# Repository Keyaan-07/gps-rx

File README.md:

# GPS Receiver
GPS-RX is a custom-hardware, low-power GPS receiver that is just 16x16mm in size. This receiver does not have any COCOM limits and is fully customisable. It uses UART to communicate with other external controllers and takes a 3.3 volt input. Unlike other GPS receivers, there are no speed or height based limits and can go to any height or any speeds. It is built like a really small module and can be built and assembled by anyone and used basically everywhere. I built this project to learn verilog and also because this seems really cool! The ice40up5k from lattice semiconductor is the FPGA that processes the GPS signals. 

### Assembly instructions
1. Order the PCB from the gerber files in the [production](/hardware/production/) folder. Get two stencils(one for the top and one for the bottom).
2. Either get PCBA, or solder the components yourself. 
3. If soldering yourself, place the top side stencil over the top side and apply paste. Place all the components. 
4. Reflow the top side. 
5. Do the same process for the bottom side!
6. Program the firmware by connecting to the test points. 
7. Your receiver is ready!

### Note about firmware: GPS firmware development without the actual board will be really hard, thus i am not writing the firmware right now. 

## BOM
|Designator                         |Function                    |Value              |Footprint                                  |Quantity|Price        |Amount|Link                                                                                                                                |
|-----------------------------------|----------------------------|-------------------|-------------------------------------------|--------|-------------|------|------------------------------------------------------------------------------------------------------------------------------------|
|PCB+stencil                        |PCB+stencil                 |Front and back both|16x16mm                                    |5+2     |2.1+6.14     |8.24  |https://jlcpcb.com/                                                                                                                 |
|C11, C9                            |Capacitor                   |100p               |402                                        |50      |0.0112       |0.56  |https://www.lcsc.com/product-detail/C77177.html                                                                                     |
|C12, C13, C14, C15, C18, C2, C4, C8|Capacitor                   |100n               |402                                        |100     |0.0067       |0.67  |https://www.lcsc.com/product-detail/C60474.html                                                                                     |
|C19                                |Capacitor                   |27p                |402                                        |100     |0.0036       |0.36  |https://www.lcsc.com/product-detail/C1557.html                                                                                      |
|C20, C23, C24, C3, C5              |Capacitor                   |470p               |402                                        |50      |0.0176       |0.88  |https://www.lcsc.com/product-detail/C76971.html                                                                                     |
|C21, C22                           |Capacitor                   |10u                |603                                        |10      |0.04         |0.4   |https://www.lcsc.com/product-detail/C18164635.html                                                                                  |
|C6                                 |Capacitor                   |10n                |402                                        |100     |0.0041       |0.41  |https://www.lcsc.com/product-detail/C5137480.html                                                                                   |
|D1                                 |LED                         |LED                |402                                        |20      |0.0357       |0.714 |https://www.lcsc.com/product-detail/C5123495.html                                                                                   |
|FL1                                |Filter                      |SAFFB1G56KB0F0A    |Filter_1109-5_1.1x0.9mm                    |10      |0.072        |0.72  |https://www.lcsc.com/product-detail/C91647.html                                                                                     |
|J1, J2                             |Connector                   |Conn_Coaxial_Small |U.FL_Molex_MCRF_73412-0110_Vertical        |5       |0.1019       |0.51  |https://www.lcsc.com/product-detail/C88374.html                                                                                     |
|J3                                 |Connector                   |Conn_01x04_Pin     |PinHeader_1x04_P2.54mm_Vertical            |20      |0.026        |0.52  |https://www.lcsc.com/product-detail/C2691448.html                                                                                   |
|L1                                 |Inductor                    |27n                |402                                        |10      |0.09         |0.9   |https://www.lcsc.com/product-detail/C882469.html                                                                                    |
|L2                                 |Inductor                    |2.2u               |402                                        |5       |0.304        |1.52  |https://www.lcsc.com/product-detail/C3911260.html                                                                                   |
|R1, R2, R6                         |Resistor                    |10k                |402                                        |100     |0.0025       |0.25  |https://www.lcsc.com/product-detail/C2906861.html                                                                                   |
|R3                                 |Resistor                    |1k                 |402                                        |100     |0.0041       |0.41  |https://www.lcsc.com/product-detail/C106235.html                                                                                    |
|R4                                 |Resistor                    |20k                |402                                        |100     |0.005        |0.5   |https://www.lcsc.com/product-detail/C93942.html                                                                                     |
|U2                                 |FPGA                        |ICE40UP5K-SG48I    |QFN-48-1EP_7x7mm_P0.5mm_EP5.6x5.6mm        |1       |8.56         |8.56  |https://www.lcsc.com/product-detail/C2678152.html                                                                                   |
|U3                                 |GPS Frontend                |MAX2769C           |TQFN-28-1EP_5x5mm_P0.5mm_EP3.25x3.25mm     |1       |3.24         |3.24  |https://www.lcsc.com/product-detail/C400150.html                                                                                    |
|U4                                 |Buck                        |PAM2305CGF120      |DFN-6-1EP_2x2mm_P0.65mm_EP1x1.6mm          |5       |0.198        |0.99  |https://www.lcsc.com/product-detail/C110511.html                                                                                    |
|U5                                 |qSPI storage                |W25Q16JVUXIQ       |Winbond_USON-8-1EP_3x2mm_P0.5mm_EP0.2x1.6mm|1       |1.62         |1.62  |https://www.lcsc.com/product-detail/C2843335.html                                                                                   |
|Y1                                 |TXCO Crystal 16.368MHz      |1XXB16368MBA       |Crystal_SMD_2520-4Pin_2.5x2.0mm            |1       |0.95         |0.95  |https://www.lcsc.com/product-detail/C213423.html                                                                                    |
|Hot air gun                        |For soldering dual sided PCB|                   |                                           |1       |45.18        |45.18 |https://robu.in/product/yihua-959d-ii-hot-air-gun-with-easy-nozzle-plug-pull-storage-stand-desoldering-smd-rework-soldering-station/|
|                                   |                            |                   |                                           |        |Subtotal     |69.864|                                                                                                                                    |
|                                   |                            |                   |                                           |        |JLC Shipping |13    |                                                                                                                                    |
|                                   |                            |                   |                                           |        |LCSC Shipping|9.26  |                                                                                                                                    |
|                                   |                            |                   |                                           |        |Total        |92.124|                                                                                                                                    |

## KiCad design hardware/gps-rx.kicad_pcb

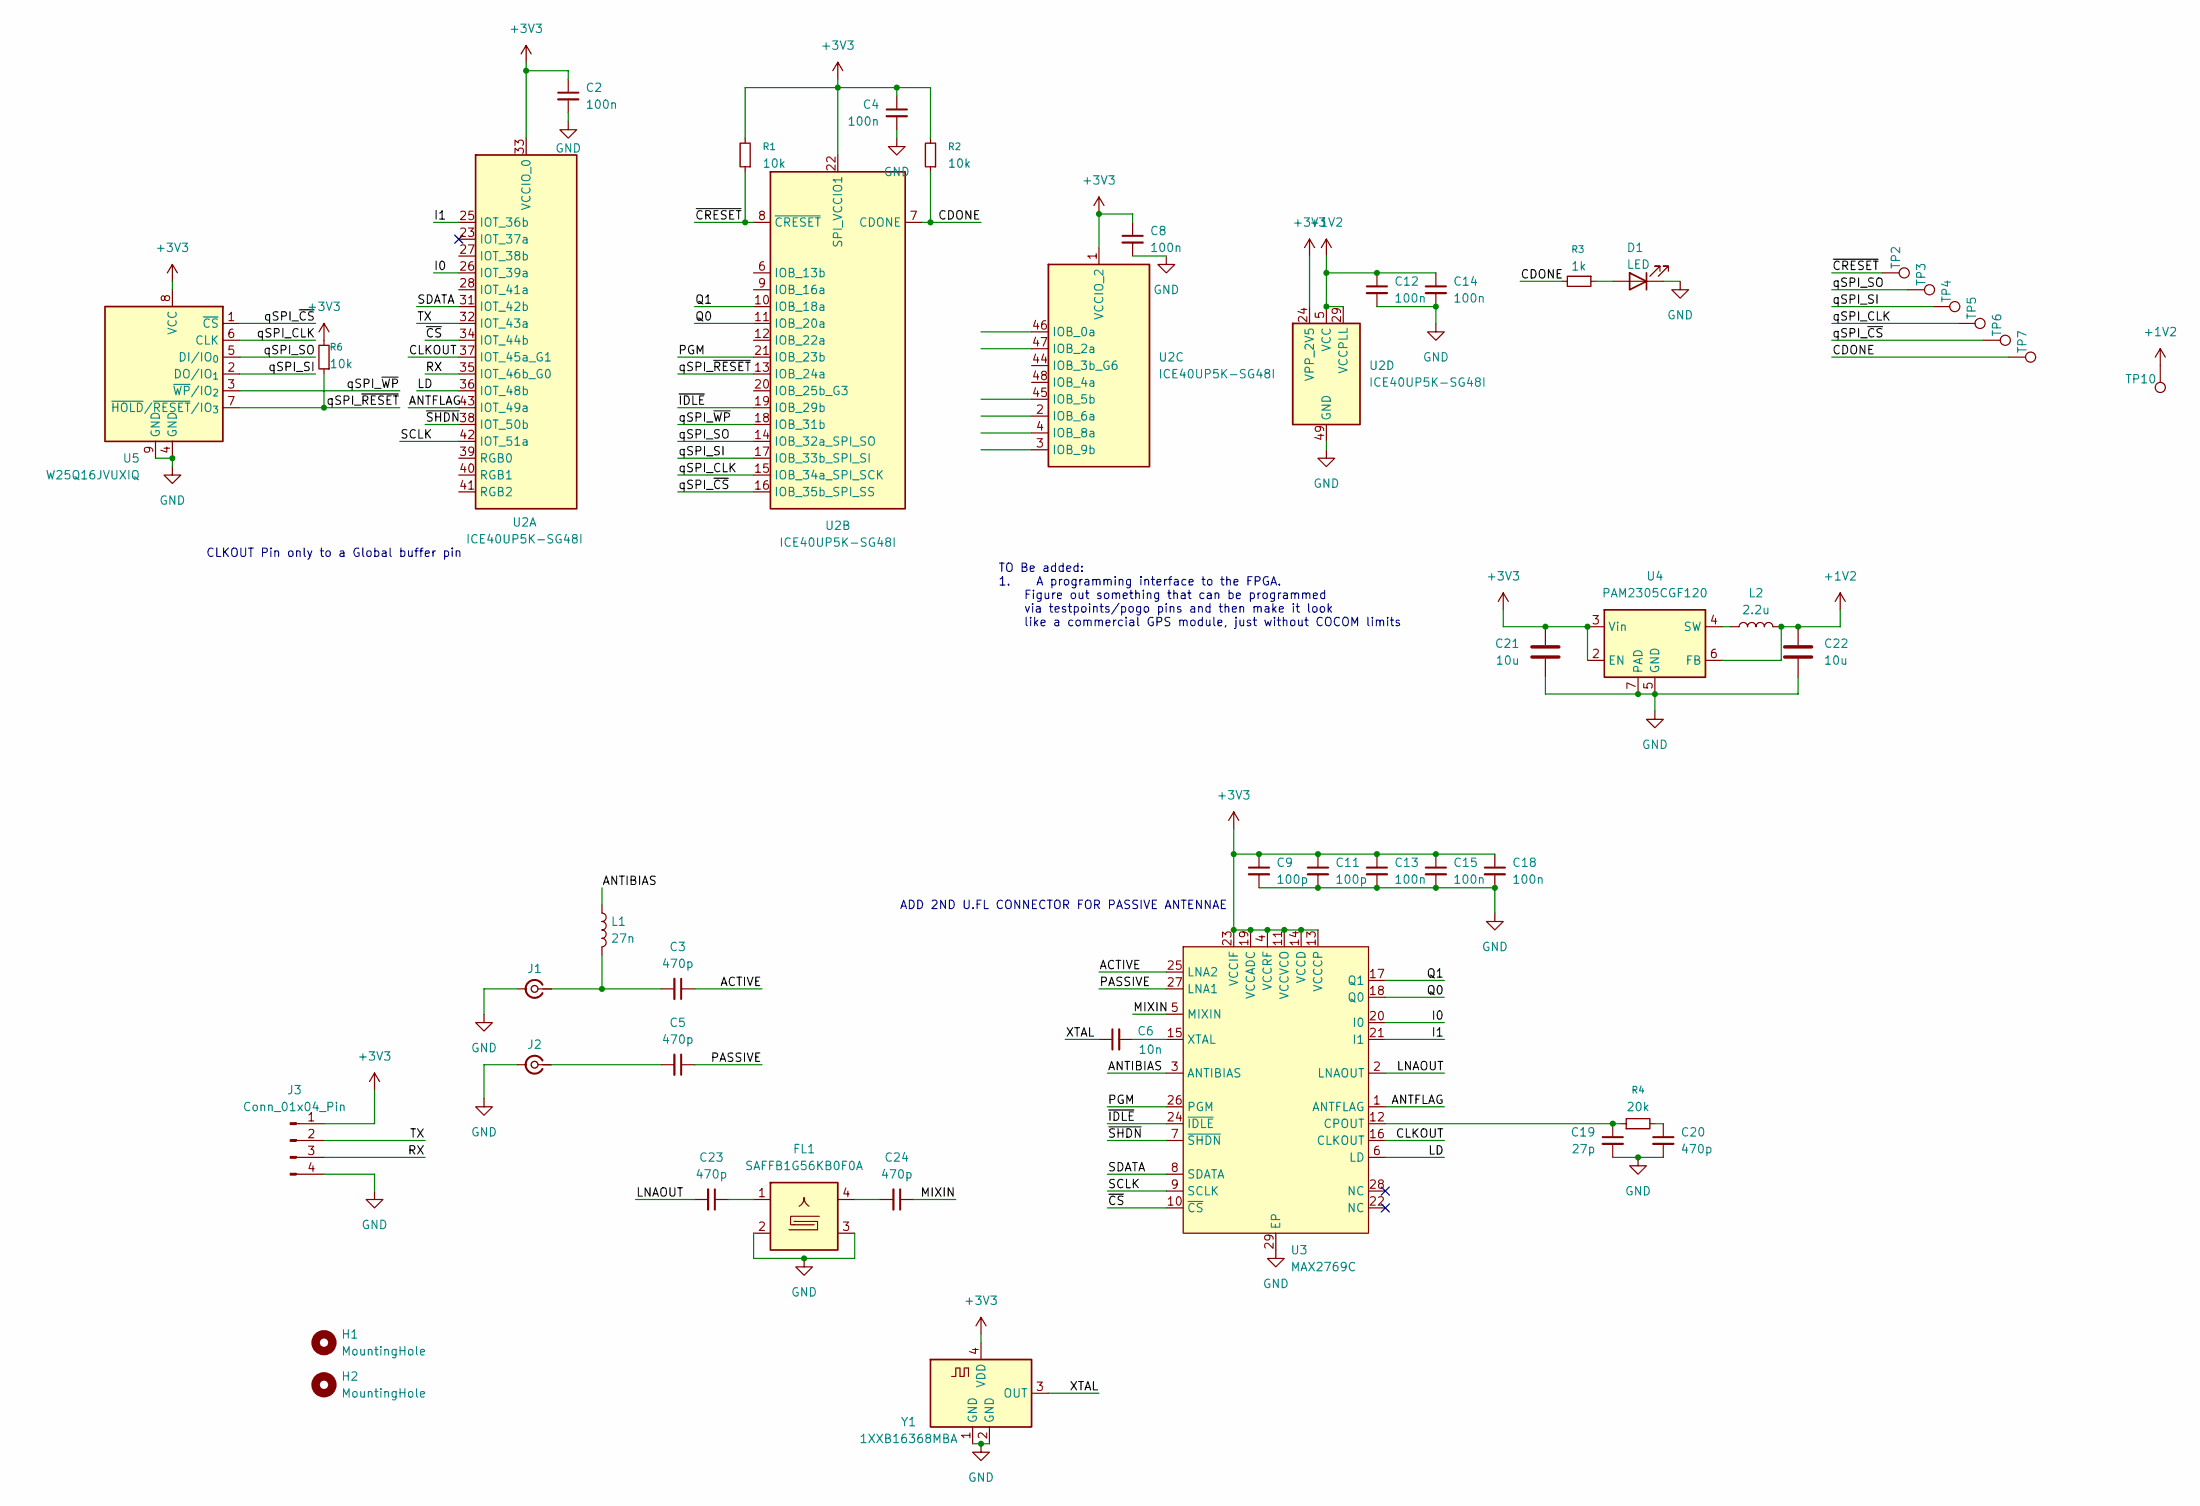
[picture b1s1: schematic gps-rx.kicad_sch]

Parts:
C2, C4, C8, C12, C13, C14, C15, C18: 100n; C_0402_1005Metric
C3, C5, C20, C23, C24: 470p; C_0402_1005Metric
C6: 10n; C_0402_1005Metric
C9, C11: 100p; C_0402_1005Metric
C19: 27p; C_0402_1005Metric
C21, C22: 10u; C_0603_1608Metric
D1: LED; LED_0402_1005Metric
FL1: SAFFB1G56KB0F0A; Filter_1109-5_1.1x0.9mm
H1, H2: MountingHole; MountingHole_2.2mm_M2
J1, J2: Conn_Coaxial_Small; U.FL_Molex_MCRF_73412-0110_Vertical
J3: Conn_01x04_Pin; PinHeader_1x04_P2.54mm_Vertical
L1: 27n; L_0402_1005Metric
L2: 2.2u; L_0402_1005Metric
R1, R2, R6: 10k; R_0402_1005Metric
R3: 1k; R_0402_1005Metric
R4: 20k; R_0402_1005Metric
TP2, TP3, TP4, TP5, TP6, TP7, TP10: TestPoint; TestPoint_Pad_D1.0mm
U2: ICE40UP5K-SG48I; QFN-48-1EP_7x7mm_P0.5mm_EP5.6x5.6mm
U3: MAX2769C; TQFN-28-1EP_5x5mm_P0.5mm_EP3.25x3.25mm
U4: PAM2305CGF120; DFN-6-1EP_2x2mm_P0.65mm_EP1x1.6mm
U5: W25Q16JVUXIQ; Winbond_USON-8-1EP_3x2mm_P0.5mm_EP0.2x1.6mm
Y1: 1XXB16368MBA; Crystal_SMD_2520-4Pin_2.5x2.0mm

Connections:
+1V2: C12.1, C14.1, C22.1, L2.2, TP10.1 (1_1), U2.5 (VCC), U2.29 (VCCPLL), U2.30 (VCC), U4.6 (FB)
+3V3: C2.1, C4.1, C8.1, C9.1, C11.1, C13.1, C15.1, C18.1, C21.1, J3.1, R1.2, R2.2, R6.2, U2.1 (VCCIO_2), U2.22 (SPI_VCCIO1), U2.24 (VPP_2V5), U2.33 (VCCIO_0), U3.4 (VCCRF), U3.11 (VCCVCO), U3.13 (VCCCP), U3.14 (VCCD), U3.19 (VCCADC), U3.23 (VCCIF), U4.2 (EN), U4.3 (Vin), U5.8 (VCC), Y1.4 (VDD)
/ACTIVE: C3.1, U3.25 (LNA2)
/ANTFLAG: U2.43 (IOT_49a), U3.1 (ANTFLAG)
/ANTIBIAS: L1.1, U3.3 (ANTIBIAS)
/CDONE: R2.1, R3.2, TP7.1 (1_1), U2.7 (CDONE)
/CLKOUT: U2.37 (IOT_45a_G1), U3.16 (CLKOUT)
/I0: U2.26 (IOT_39a), U3.20 (I0)
/I1: U2.25 (IOT_36b), U3.21 (I1)
/LD: U2.36 (IOT_48b), U3.6 (LD)
/LNAOUT: C23.2, U3.2 (LNAOUT)
/MIXIN: C24.1, U3.5 (MIXIN)
/PASSIVE: C5.1, U3.27 (LNA1)
/PGM: U2.21 (IOB_23b), U3.26 (PGM)
/Q0: U2.11 (IOB_20a), U3.18 (Q0)
/Q1: U2.10 (IOB_18a), U3.17 (Q1)
/RX: J3.3, U2.35 (IOT_46b_G0)
/SCLK: U2.42 (IOT_51a), U3.9 (SCLK)
/SDATA: U2.31 (IOT_42b), U3.8 (SDATA)
/TX: J3.2, U2.32 (IOT_43a)
/XTAL: C6.1, Y1.3 (OUT)
/qSPI_CLK: TP5.1 (1_1), U2.15 (IOB_34a_SPI_SCK), U5.6 (CLK)
/qSPI_SI: TP4.1 (1_1), U2.17 (IOB_33b_SPI_SI), U5.2 (DO/IO_{1})
/qSPI_SO: TP3.1 (1_1), U2.14 (IOB_32a_SPI_SO), U5.5 (DI/IO_{0})
/qSPI_~CS: TP6.1 (1_1), U2.16 (IOB_35b_SPI_SS), U5.1 (~CS)
/qSPI_~RESET: R6.1, U2.13 (IOB_24a), U5.7 (~HOLD/~RESET/IO_{3})
/qSPI_~WP: U2.18 (IOB_31b), U5.3 (~WP/IO_{2})
/~CRESET: R1.1, TP2.1 (1_1), U2.8 (~CRESET)
/~CS: U2.34 (IOT_44b), U3.10 (~CS)
/~IDLE: U2.19 (IOB_29b), U3.24 (~IDLE)
/~SHDN: U2.38 (IOT_50b), U3.7 (~SHDN)
GND: C2.2, C4.2, C8.2, C9.2, C11.2, C12.2, C13.2, C14.2, C15.2, C18.2, C19.2, C20.2, C21.2, C22.2, D1.1 (K), FL1.2, FL1.3, FL1.5, J1.2 (Ext), J2.2 (Ext), J3.4, U2.49 (GND), U3.29 (EP), U4.5 (GND), U4.7 (PAD), U5.4 (GND), U5.9 (GND), Y1.1 (GND), Y1.2 (GND)
unnamed: C20.1, R4.2
unnamed: C23.1, FL1.1
unnamed: C24.2, FL1.4
unnamed: D1.2 (A), R3.1
unnamed: C3.2, J1.1 (In), L1.2
unnamed: C5.2, J2.1 (In)
unnamed: C19.1, R4.1, U3.12 (CPOUT)
unnamed: C6.2, U3.15 (XTAL)
unnamed: L2.1, U4.4 (SW)

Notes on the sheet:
CLKOUT Pin only to a Global buffer pin
ADD 2ND U.FL CONNECTOR FOR PASSIVE ANTENNAE
TO Be added: 1. A programming interface to the FPGA. Figure out something that can be programmed via testpoints/pogo pins and then make it look like a commercial GPS module, just without COCOM limits

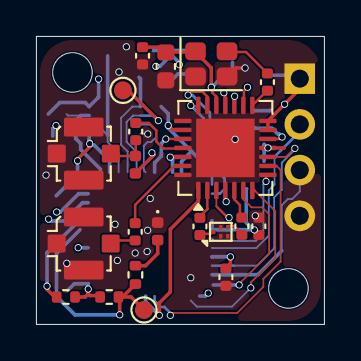
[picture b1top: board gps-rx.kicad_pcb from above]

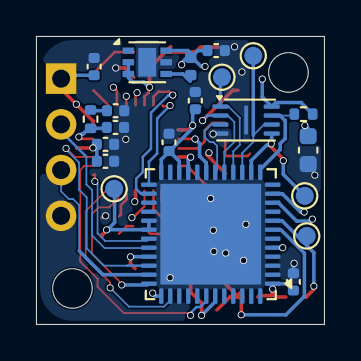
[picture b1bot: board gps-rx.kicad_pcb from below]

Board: 4 copper layers, 16.0 x 16.0 mm, 45 parts (22 on the bottom side), 41 nets.

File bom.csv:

Designator,Function,Value,Footprint,Quantity,Price,Amount,Link
PCB+stencil,PCB+stencil,Front and back both,16x16mm,5+2,2.1+6.14,8.24,https://jlcpcb.com/
"C11, C9",Capacitor,100p,402,50,0.0112,0.56,https://www.lcsc.com/product-detail/C77177.html
"C12, C13, C14, C15, C18, C2, C4, C8",Capacitor,100n,402,100,0.0067,0.67,https://www.lcsc.com/product-detail/C60474.html
C19,Capacitor,27p,402,100,0.0036,0.36,https://www.lcsc.com/product-detail/C1557.html
"C20, C23, C24, C3, C5",Capacitor,470p,402,50,0.0176,0.88,https://www.lcsc.com/product-detail/C76971.html
"C21, C22",Capacitor,10u,603,10,0.04,0.4,https://www.lcsc.com/product-detail/C18164635.html
C6,Capacitor,10n,402,100,0.0041,0.41,https://www.lcsc.com/product-detail/C5137480.html
D1,LED,LED,402,20,0.0357,0.714,https://www.lcsc.com/product-detail/C5123495.html
FL1,Filter,SAFFB1G56KB0F0A,Filter_1109-5_1.1x0.9mm,10,0.072,0.72,https://www.lcsc.com/product-detail/C91647.html
"J1, J2",Connector,Conn_Coaxial_Small,U.FL_Molex_MCRF_73412-0110_Vertical,5,0.1019,0.51,https://www.lcsc.com/product-detail/C88374.html
J3,Connector,Conn_01x04_Pin,PinHeader_1x04_P2.54mm_Vertical,20,0.026,0.52,https://www.lcsc.com/product-detail/C2691448.html
L1,Inductor,27n,402,10,0.09,0.9,https://www.lcsc.com/product-detail/C882469.html
L2,Inductor,2.2u,402,5,0.304,1.52,https://www.lcsc.com/product-detail/C3911260.html
"R1, R2, R6",Resistor,10k,402,100,0.0025,0.25,https://www.lcsc.com/product-detail/C2906861.html
R3,Resistor,1k,402,100,0.0041,0.41,https://www.lcsc.com/product-detail/C106235.html
R4,Resistor,20k,402,100,0.005,0.5,https://www.lcsc.com/product-detail/C93942.html
U2,FPGA,ICE40UP5K-SG48I,QFN-48-1EP_7x7mm_P0.5mm_EP5.6x5.6mm,1,8.56,8.56,https://www.lcsc.com/product-detail/C2678152.html
U3,GPS Frontend,MAX2769C,TQFN-28-1EP_5x5mm_P0.5mm_EP3.25x3.25mm,1,3.24,3.24,https://www.lcsc.com/product-detail/C400150.html
U4,Buck,PAM2305CGF120,DFN-6-1EP_2x2mm_P0.65mm_EP1x1.6mm,5,0.198,0.99,https://www.lcsc.com/product-detail/C110511.html
U5,qSPI storage,W25Q16JVUXIQ,Winbond_USON-8-1EP_3x2mm_P0.5mm_EP0.2x1.6mm,1,1.62,1.62,https://www.lcsc.com/product-detail/C2843335.html
Y1,TXCO Crystal 16.368MHz,1XXB16368MBA,Crystal_SMD_2520-4Pin_2.5x2.0mm,1,0.95,0.95,https://www.lcsc.com/product-detail/C213423.html
Hot air gun,For soldering dual sided PCB,,,1,45.18,45.18,https://robu.in/product/yihua-959d-ii-hot-air-gun-with-easy-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
,,,,,Subtotal,69.864,
,,,,,JLC Shipping,13,
,,,,,LCSC Shipping,9.26,
,,,,,Total,92.124,

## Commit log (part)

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2026-06-28 Hello World
2026-06-28 added gitignore
2026-06-28 new project specific library
